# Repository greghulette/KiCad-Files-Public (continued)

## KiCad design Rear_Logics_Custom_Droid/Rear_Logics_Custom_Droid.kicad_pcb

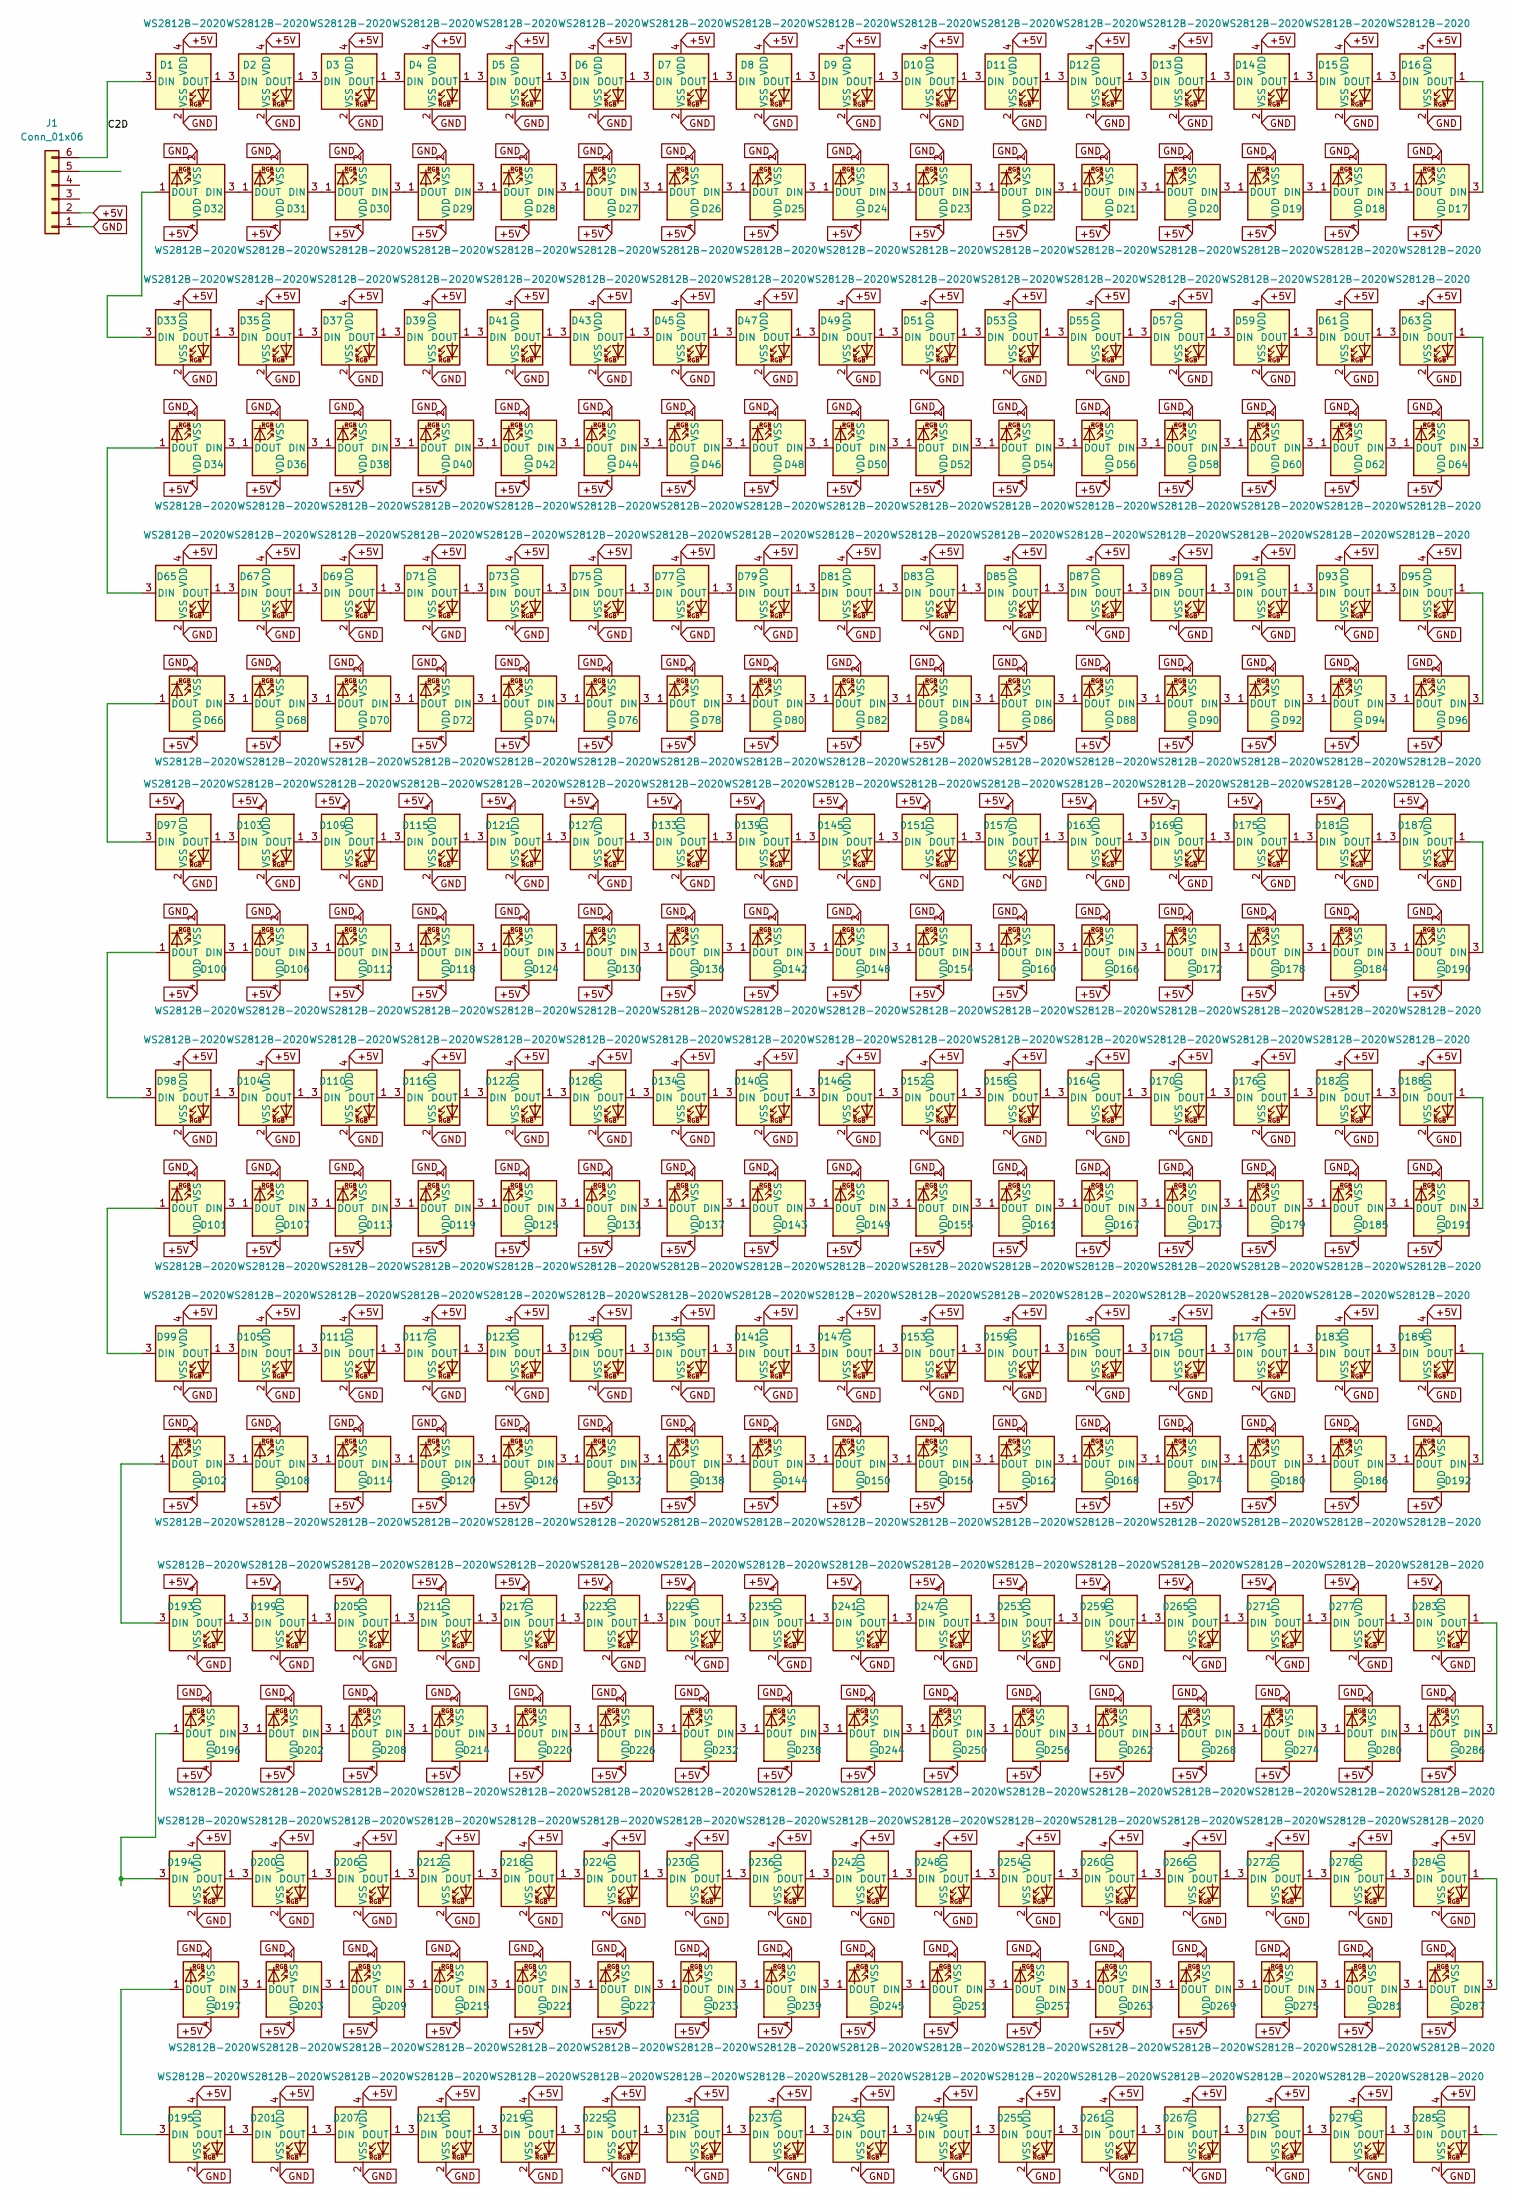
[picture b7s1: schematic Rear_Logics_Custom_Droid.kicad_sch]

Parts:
D1, D2, D3, D4, D5, D6, D7, D8, D9, D10, D11, D12, D13, D14, D15, D16, D17, D18, D19, D20, D21, D22, D23, D24, D25, D26, D27, D28, D29, D30, D31, D32, D33, D34, D35, D36, D37, D38, D39, D40, D41, D42, D43, D44, D45, D46, D47, D48, D49, D50, D51, D52, D53, D54, D55, D56, D57, D58, D59, D60, D61, D62, D63, D64, D65, D66, D67, D68, D69, D70, D71, D72, D73, D74, D75, D76, D77, D78, D79, D80, D81, D82, D83, D84, D85, D86, D87, D88, D89, D90, D91, D92, D93, D94, D95, D96, D97, D98, D99, D100, D101, D102, D103, D104, D105, D106, D107, D108, D109, D110, D111, D112, D113, D114, D115, D116, D117, D118, D119, D120, D121, D122, D123, D124, D125, D126, D127, D128, D129, D130, D131, D132, D133, D134, D135, D136, D137, D138, D139, D140, D141, D142, D143, D144, D145, D146, D147, D148, D149, D150, D151, D152, D153, D154, D155, D156, D157, D158, D159, D160, D161, D162, D163, D164, D165, D166, D167, D168, D169, D170, D171, D172, D173, D174, D175, D176, D177, D178, D179, D180, D181, D182, D183, D184, D185, D186, D187, D188, D189, D190, D191, D192, D193, D194, D195, D196, D197, D199, D200, D201, D202, D203, D205, D206, D207, D208, D209, D211, D212, D213, D214, D215, D217, D218, D219, D220, D221, D223, D224, D225, D226, D227, D229, D230, D231, D232, D233, D235, D236, D237, D238, D239, D241, D242, D243, D244, D245, D247, D248, D249, D250, D251, D253, D254, D255, D256, D257, D259, D260, D261, D262, D263, D265, D266, D267, D268, D269, D271, D272, D273, D274, D275, D277, D278, D279, D280, D281, D283, D284, D285, D286, D287: WS2812B-2020; LED_WS2812B-2020_PLCC4_2.0x2.0mm
J1: Conn_01x06; PinHeader_1x06_P2.54mm_Vertical

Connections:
+5V: D1.4 (VDD), D2.4 (VDD), D3.4 (VDD), D4.4 (VDD), D5.4 (VDD), D6.4 (VDD), D7.4 (VDD), D8.4 (VDD), D9.4 (VDD), D10.4 (VDD), D11.4 (VDD), D12.4 (VDD), D13.4 (VDD), D14.4 (VDD), D15.4 (VDD), D16.4 (VDD), D17.4 (VDD), D18.4 (VDD), D19.4 (VDD), D20.4 (VDD), D21.4 (VDD), D22.4 (VDD), D23.4 (VDD), D24.4 (VDD), D25.4 (VDD), D26.4 (VDD), D27.4 (VDD), D28.4 (VDD), D29.4 (VDD), D30.4 (VDD), D31.4 (VDD), D32.4 (VDD), D33.4 (VDD), D34.4 (VDD), D35.4 (VDD), D36.4 (VDD), D37.4 (VDD), D38.4 (VDD), D39.4 (VDD), D40.4 (VDD), D41.4 (VDD), D42.4 (VDD), D43.4 (VDD), D44.4 (VDD), D45.4 (VDD), D46.4 (VDD), D47.4 (VDD), D48.4 (VDD), D49.4 (VDD), D50.4 (VDD), D51.4 (VDD), D52.4 (VDD), D53.4 (VDD), D54.4 (VDD), D55.4 (VDD), D56.4 (VDD), D57.4 (VDD), D58.4 (VDD), D59.4 (VDD), D60.4 (VDD), D61.4 (VDD), D62.4 (VDD), D63.4 (VDD), D64.4 (VDD), D65.4 (VDD), D66.4 (VDD), D67.4 (VDD), D68.4 (VDD), D69.4 (VDD), D70.4 (VDD), D71.4 (VDD), D72.4 (VDD), D73.4 (VDD), D74.4 (VDD), D75.4 (VDD), D76.4 (VDD), D77.4 (VDD), D78.4 (VDD), D79.4 (VDD), D80.4 (VDD), D81.4 (VDD), D82.4 (VDD), D83.4 (VDD), D84.4 (VDD), D85.4 (VDD), D86.4 (VDD), D87.4 (VDD), D88.4 (VDD), D89.4 (VDD), D90.4 (VDD), D91.4 (VDD), D92.4 (VDD), D93.4 (VDD), D94.4 (VDD), D95.4 (VDD), D96.4 (VDD), D97.4 (VDD), D98.4 (VDD), D99.4 (VDD), D100.4 (VDD), D101.4 (VDD), D102.4 (VDD), D103.4 (VDD), D104.4 (VDD), D105.4 (VDD), D106.4 (VDD), D107.4 (VDD), D108.4 (VDD), D109.4 (VDD), D110.4 (VDD), D111.4 (VDD), D112.4 (VDD), D113.4 (VDD), D114.4 (VDD), D115.4 (VDD), D116.4 (VDD), D117.4 (VDD), D118.4 (VDD), D119.4 (VDD), D120.4 (VDD), D121.4 (VDD), D122.4 (VDD), D123.4 (VDD), D124.4 (VDD), D125.4 (VDD), D126.4 (VDD), D127.4 (VDD), D128.4 (VDD), D129.4 (VDD), D130.4 (VDD), D131.4 (VDD), D132.4 (VDD), D133.4 (VDD), D134.4 (VDD), D135.4 (VDD), D136.4 (VDD), D137.4 (VDD), D138.4 (VDD), D139.4 (VDD), D140.4 (VDD), D141.4 (VDD), D142.4 (VDD), D143.4 (VDD), D144.4 (VDD), D145.4 (VDD), D146.4 (VDD), D147.4 (VDD), D148.4 (VDD), D149.4 (VDD), D150.4 (VDD), D151.4 (VDD), D152.4 (VDD), D153.4 (VDD), D154.4 (VDD), D155.4 (VDD), D156.4 (VDD), D157.4 (VDD), D158.4 (VDD), D159.4 (VDD), D160.4 (VDD), D161.4 (VDD), D162.4 (VDD), D163.4 (VDD), D164.4 (VDD), D165.4 (VDD), D166.4 (VDD), D167.4 (VDD), D168.4 (VDD), D169.4 (VDD), D170.4 (VDD), D171.4 (VDD), D172.4 (VDD), D173.4 (VDD), D174.4 (VDD), D175.4 (VDD), D176.4 (VDD), D177.4 (VDD), D178.4 (VDD), D179.4 (VDD), D180.4 (VDD), D181.4 (VDD), D182.4 (VDD), D183.4 (VDD), D184.4 (VDD), D185.4 (VDD), D186.4 (VDD), D187.4 (VDD), D188.4 (VDD), D189.4 (VDD), D190.4 (VDD), D191.4 (VDD), D192.4 (VDD), D193.4 (VDD), D194.4 (VDD), D195.4 (VDD), D196.4 (VDD), D197.4 (VDD), D199.4 (VDD), D200.4 (VDD), D201.4 (VDD), D202.4 (VDD), D203.4 (VDD), D205.4 (VDD), D206.4 (VDD), D207.4 (VDD), D208.4 (VDD), D209.4 (VDD), D211.4 (VDD), D212.4 (VDD), D213.4 (VDD), D214.4 (VDD), D215.4 (VDD), D217.4 (VDD), D218.4 (VDD), D219.4 (VDD), D220.4 (VDD), D221.4 (VDD), D223.4 (VDD), D224.4 (VDD), D225.4 (VDD), D226.4 (VDD), D227.4 (VDD), D229.4 (VDD), D230.4 (VDD), D231.4 (VDD), D232.4 (VDD), D233.4 (VDD), D235.4 (VDD), D236.4 (VDD), D237.4 (VDD), D238.4 (VDD), D239.4 (VDD), D241.4 (VDD), D242.4 (VDD), D243.4 (VDD), D244.4 (VDD), D245.4 (VDD), D247.4 (VDD), D248.4 (VDD), D249.4 (VDD), D250.4 (VDD), D251.4 (VDD), D253.4 (VDD), D254.4 (VDD), D255.4 (VDD), D256.4 (VDD), D257.4 (VDD), D259.4 (VDD), D260.4 (VDD), D261.4 (VDD), D262.4 (VDD), D263.4 (VDD), D265.4 (VDD), D266.4 (VDD), D267.4 (VDD), D268.4 (VDD), D269.4 (VDD), D271.4 (VDD), D272.4 (VDD), D273.4 (VDD), D274.4 (VDD), D275.4 (VDD), D277.4 (VDD), D278.4 (VDD), D279.4 (VDD), D280.4 (VDD), D281.4 (VDD), D283.4 (VDD), D284.4 (VDD), D285.4 (VDD), D286.4 (VDD), D287.4 (VDD), J1.2
/C2D: D1.3 (DIN), J1.6
GND: D1.2 (VSS), D2.2 (VSS), D3.2 (VSS), D4.2 (VSS), D5.2 (VSS), D6.2 (VSS), D7.2 (VSS), D8.2 (VSS), D9.2 (VSS), D10.2 (VSS), D11.2 (VSS), D12.2 (VSS), D13.2 (VSS), D14.2 (VSS), D15.2 (VSS), D16.2 (VSS), D17.2 (VSS), D18.2 (VSS), D19.2 (VSS), D20.2 (VSS), D21.2 (VSS), D22.2 (VSS), D23.2 (VSS), D24.2 (VSS), D25.2 (VSS), D26.2 (VSS), D27.2 (VSS), D28.2 (VSS), D29.2 (VSS), D30.2 (VSS), D31.2 (VSS), D32.2 (VSS), D33.2 (VSS), D34.2 (VSS), D35.2 (VSS), D36.2 (VSS), D37.2 (VSS), D38.2 (VSS), D39.2 (VSS), D40.2 (VSS), D41.2 (VSS), D42.2 (VSS), D43.2 (VSS), D44.2 (VSS), D45.2 (VSS), D46.2 (VSS), D47.2 (VSS), D48.2 (VSS), D49.2 (VSS), D50.2 (VSS), D51.2 (VSS), D52.2 (VSS), D53.2 (VSS), D54.2 (VSS), D55.2 (VSS), D56.2 (VSS), D57.2 (VSS), D58.2 (VSS), D59.2 (VSS), D60.2 (VSS), D61.2 (VSS), D62.2 (VSS), D63.2 (VSS), D64.2 (VSS), D65.2 (VSS), D66.2 (VSS), D67.2 (VSS), D68.2 (VSS), D69.2 (VSS), D70.2 (VSS), D71.2 (VSS), D72.2 (VSS), D73.2 (VSS), D74.2 (VSS), D75.2 (VSS), D76.2 (VSS), D77.2 (VSS), D78.2 (VSS), D79.2 (VSS), D80.2 (VSS), D81.2 (VSS), D82.2 (VSS), D83.2 (VSS), D84.2 (VSS), D85.2 (VSS), D86.2 (VSS), D87.2 (VSS), D88.2 (VSS), D89.2 (VSS), D90.2 (VSS), D91.2 (VSS), D92.2 (VSS), D93.2 (VSS), D94.2 (VSS), D95.2 (VSS), D96.2 (VSS), D97.2 (VSS), D98.2 (VSS), D99.2 (VSS), D100.2 (VSS), D101.2 (VSS), D102.2 (VSS), D103.2 (VSS), D104.2 (VSS), D105.2 (VSS), D106.2 (VSS), D107.2 (VSS), D108.2 (VSS), D109.2 (VSS), D110.2 (VSS), D111.2 (VSS), D112.2 (VSS), D113.2 (VSS), D114.2 (VSS), D115.2 (VSS), D116.2 (VSS), D117.2 (VSS), D118.2 (VSS), D119.2 (VSS), D120.2 (VSS), D121.2 (VSS), D122.2 (VSS), D123.2 (VSS), D124.2 (VSS), D125.2 (VSS), D126.2 (VSS), D127.2 (VSS), D128.2 (VSS), D129.2 (VSS), D130.2 (VSS), D131.2 (VSS), D132.2 (VSS), D133.2 (VSS), D134.2 (VSS), D135.2 (VSS), D136.2 (VSS), D137.2 (VSS), D138.2 (VSS), D139.2 (VSS), D140.2 (VSS), D141.2 (VSS), D142.2 (VSS), D143.2 (VSS), D144.2 (VSS), D145.2 (VSS), D146.2 (VSS), D147.2 (VSS), D148.2 (VSS), D149.2 (VSS), D150.2 (VSS), D151.2 (VSS), D152.2 (VSS), D153.2 (VSS), D154.2 (VSS), D155.2 (VSS), D156.2 (VSS), D157.2 (VSS), D158.2 (VSS), D159.2 (VSS), D160.2 (VSS), D161.2 (VSS), D162.2 (VSS), D163.2 (VSS), D164.2 (VSS), D165.2 (VSS), D166.2 (VSS), D167.2 (VSS), D168.2 (VSS), D169.2 (VSS), D170.2 (VSS), D171.2 (VSS), D172.2 (VSS), D173.2 (VSS), D174.2 (VSS), D175.2 (VSS), D176.2 (VSS), D177.2 (VSS), D178.2 (VSS), D179.2 (VSS), D180.2 (VSS), D181.2 (VSS), D182.2 (VSS), D183.2 (VSS), D184.2 (VSS), D185.2 (VSS), D186.2 (VSS), D187.2 (VSS), D188.2 (VSS), D189.2 (VSS), D190.2 (VSS), D191.2 (VSS), D192.2 (VSS), D193.2 (VSS), D194.2 (VSS), D195.2 (VSS), D196.2 (VSS), D197.2 (VSS), D199.2 (VSS), D200.2 (VSS), D201.2 (VSS), D202.2 (VSS), D203.2 (VSS), D205.2 (VSS), D206.2 (VSS), D207.2 (VSS), D208.2 (VSS), D209.2 (VSS), D211.2 (VSS), D212.2 (VSS), D213.2 (VSS), D214.2 (VSS), D215.2 (VSS), D217.2 (VSS), D218.2 (VSS), D219.2 (VSS), D220.2 (VSS), D221.2 (VSS), D223.2 (VSS), D224.2 (VSS), D225.2 (VSS), D226.2 (VSS), D227.2 (VSS), D229.2 (VSS), D230.2 (VSS), D231.2 (VSS), D232.2 (VSS), D233.2 (VSS), D235.2 (VSS), D236.2 (VSS), D237.2 (VSS), D238.2 (VSS), D239.2 (VSS), D241.2 (VSS), D242.2 (VSS), D243.2 (VSS), D244.2 (VSS), D245.2 (VSS), D247.2 (VSS), D248.2 (VSS), D249.2 (VSS), D250.2 (VSS), D251.2 (VSS), D253.2 (VSS), D254.2 (VSS), D255.2 (VSS), D256.2 (VSS), D257.2 (VSS), D259.2 (VSS), D260.2 (VSS), D261.2 (VSS), D262.2 (VSS), D263.2 (VSS), D265.2 (VSS), D266.2 (VSS), D267.2 (VSS), D268.2 (VSS), D269.2 (VSS), D271.2 (VSS), D272.2 (VSS), D273.2 (VSS), D274.2 (VSS), D275.2 (VSS), D277.2 (VSS), D278.2 (VSS), D279.2 (VSS), D280.2 (VSS), D281.2 (VSS), D283.2 (VSS), D284.2 (VSS), D285.2 (VSS), D286.2 (VSS), D287.2 (VSS), J1.1
unnamed: D1.1 (DOUT), D2.3 (DIN)
unnamed: D2.1 (DOUT), D3.3 (DIN)
unnamed: D3.1 (DOUT), D4.3 (DIN)
unnamed: D4.1 (DOUT), D5.3 (DIN)
unnamed: D5.1 (DOUT), D6.3 (DIN)
unnamed: D6.1 (DOUT), D7.3 (DIN)
unnamed: D7.1 (DOUT), D8.3 (DIN)
unnamed: D8.1 (DOUT), D9.3 (DIN)
unnamed: D9.1 (DOUT), D10.3 (DIN)
unnamed: D10.1 (DOUT), D11.3 (DIN)
unnamed: D11.1 (DOUT), D12.3 (DIN)
unnamed: D12.1 (DOUT), D13.3 (DIN)
unnamed: D13.1 (DOUT), D14.3 (DIN)
unnamed: D14.1 (DOUT), D15.3 (DIN)
unnamed: D15.1 (DOUT), D16.3 (DIN)
unnamed: D16.1 (DOUT), D17.3 (DIN)
unnamed: D17.1 (DOUT), D18.3 (DIN)
unnamed: D18.1 (DOUT), D19.3 (DIN)
unnamed: D19.1 (DOUT), D20.3 (DIN)
unnamed: D20.1 (DOUT), D21.3 (DIN)
unnamed: D21.1 (DOUT), D22.3 (DIN)
unnamed: D22.1 (DOUT), D23.3 (DIN)
unnamed: D23.1 (DOUT), D24.3 (DIN)
unnamed: D24.1 (DOUT), D25.3 (DIN)
unnamed: D25.1 (DOUT), D26.3 (DIN)
unnamed: D26.1 (DOUT), D27.3 (DIN)
unnamed: D27.1 (DOUT), D28.3 (DIN)
unnamed: D28.1 (DOUT), D29.3 (DIN)
unnamed: D29.1 (DOUT), D30.3 (DIN)
unnamed: D30.1 (DOUT), D31.3 (DIN)
unnamed: D31.1 (DOUT), D32.3 (DIN)
unnamed: D32.1 (DOUT), D33.3 (DIN)
unnamed: D33.1 (DOUT), D35.3 (DIN)
unnamed: D34.3 (DIN), D36.1 (DOUT)
unnamed: D34.1 (DOUT), D65.3 (DIN)
unnamed: D35.1 (DOUT), D37.3 (DIN)
unnamed: D36.3 (DIN), D38.1 (DOUT)
unnamed: D37.1 (DOUT), D39.3 (DIN)
unnamed: D38.3 (DIN), D40.1 (DOUT)
unnamed: D39.1 (DOUT), D41.3 (DIN)
unnamed: D40.3 (DIN), D42.1 (DOUT)
unnamed: D41.1 (DOUT), D43.3 (DIN)
unnamed: D42.3 (DIN), D44.1 (DOUT)
unnamed: D43.1 (DOUT), D45.3 (DIN)
unnamed: D44.3 (DIN), D46.1 (DOUT)
unnamed: D45.1 (DOUT), D47.3 (DIN)
unnamed: D46.3 (DIN), D48.1 (DOUT)
unnamed: D47.1 (DOUT), D49.3 (DIN)
unnamed: D48.3 (DIN), D50.1 (DOUT)
unnamed: D49.1 (DOUT), D51.3 (DIN)
unnamed: D50.3 (DIN), D52.1 (DOUT)
unnamed: D51.1 (DOUT), D53.3 (DIN)
unnamed: D52.3 (DIN), D54.1 (DOUT)
unnamed: D53.1 (DOUT), D55.3 (DIN)
unnamed: D54.3 (DIN), D56.1 (DOUT)
unnamed: D55.1 (DOUT), D57.3 (DIN)
unnamed: D56.3 (DIN), D58.1 (DOUT)
unnamed: D57.1 (DOUT), D59.3 (DIN)
unnamed: D58.3 (DIN), D60.1 (DOUT)
unnamed: D59.1 (DOUT), D61.3 (DIN)
unnamed: D60.3 (DIN), D62.1 (DOUT)
unnamed: D61.1 (DOUT), D63.3 (DIN)
unnamed: D62.3 (DIN), D64.1 (DOUT)
unnamed: D63.1 (DOUT), D64.3 (DIN)
unnamed: D65.1 (DOUT), D67.3 (DIN)
unnamed: D66.3 (DIN), D68.1 (DOUT)
unnamed: D66.1 (DOUT), D97.3 (DIN)
unnamed: D67.1 (DOUT), D69.3 (DIN)
unnamed: D68.3 (DIN), D70.1 (DOUT)
unnamed: D69.1 (DOUT), D71.3 (DIN)
unnamed: D70.3 (DIN), D72.1 (DOUT)
unnamed: D71.1 (DOUT), D73.3 (DIN)
unnamed: D72.3 (DIN), D74.1 (DOUT)
unnamed: D73.1 (DOUT), D75.3 (DIN)
unnamed: D74.3 (DIN), D76.1 (DOUT)
unnamed: D75.1 (DOUT), D77.3 (DIN)
unnamed: D76.3 (DIN), D78.1 (DOUT)
unnamed: D77.1 (DOUT), D79.3 (DIN)
unnamed: D78.3 (DIN), D80.1 (DOUT)
unnamed: D79.1 (DOUT), D81.3 (DIN)
unnamed: D80.3 (DIN), D82.1 (DOUT)
unnamed: D81.1 (DOUT), D83.3 (DIN)
unnamed: D82.3 (DIN), D84.1 (DOUT)
unnamed: D83.1 (DOUT), D85.3 (DIN)
unnamed: D84.3 (DIN), D86.1 (DOUT)
unnamed: D85.1 (DOUT), D87.3 (DIN)
unnamed: D86.3 (DIN), D88.1 (DOUT)
unnamed: D87.1 (DOUT), D89.3 (DIN)
unnamed: D88.3 (DIN), D90.1 (DOUT)
unnamed: D89.1 (DOUT), D91.3 (DIN)
unnamed: D90.3 (DIN), D92.1 (DOUT)
unnamed: D91.1 (DOUT), D93.3 (DIN)
unnamed: D92.3 (DIN), D94.1 (DOUT)
unnamed: D93.1 (DOUT), D95.3 (DIN)
unnamed: D94.3 (DIN), D96.1 (DOUT)
unnamed: D95.1 (DOUT), D96.3 (DIN)
unnamed: D100.3 (DIN), D106.1 (DOUT)
unnamed: D98.3 (DIN), D100.1 (DOUT)
unnamed: D101.3 (DIN), D107.1 (DOUT)
unnamed: D99.3 (DIN), D101.1 (DOUT)
unnamed: D102.3 (DIN), D108.1 (DOUT)
unnamed: D102.1 (DOUT), D193.3 (DIN)
unnamed: D97.1 (DOUT), D103.3 (DIN)
unnamed: D103.1 (DOUT), D109.3 (DIN)
unnamed: D98.1 (DOUT), D104.3 (DIN)
unnamed: D104.1 (DOUT), D110.3 (DIN)
unnamed: D99.1 (DOUT), D105.3 (DIN)
unnamed: D105.1 (DOUT), D111.3 (DIN)
unnamed: D106.3 (DIN), D112.1 (DOUT)
unnamed: D107.3 (DIN), D113.1 (DOUT)
unnamed: D108.3 (DIN), D114.1 (DOUT)
unnamed: D109.1 (DOUT), D115.3 (DIN)
unnamed: D110.1 (DOUT), D116.3 (DIN)
unnamed: D111.1 (DOUT), D117.3 (DIN)
unnamed: D112.3 (DIN), D118.1 (DOUT)
unnamed: D113.3 (DIN), D119.1 (DOUT)
unnamed: D114.3 (DIN), D120.1 (DOUT)
unnamed: D115.1 (DOUT), D121.3 (DIN)
unnamed: D116.1 (DOUT), D122.3 (DIN)
unnamed: D117.1 (DOUT), D123.3 (DIN)
unnamed: D118.3 (DIN), D124.1 (DOUT)
unnamed: D119.3 (DIN), D125.1 (DOUT)
unnamed: D120.3 (DIN), D126.1 (DOUT)
unnamed: D121.1 (DOUT), D127.3 (DIN)
unnamed: D122.1 (DOUT), D128.3 (DIN)
unnamed: D123.1 (DOUT), D129.3 (DIN)
unnamed: D124.3 (DIN), D130.1 (DOUT)
unnamed: D125.3 (DIN), D131.1 (DOUT)
unnamed: D126.3 (DIN), D132.1 (DOUT)
unnamed: D127.1 (DOUT), D133.3 (DIN)
unnamed: D128.1 (DOUT), D134.3 (DIN)
unnamed: D129.1 (DOUT), D135.3 (DIN)
unnamed: D130.3 (DIN), D136.1 (DOUT)
unnamed: D131.3 (DIN), D137.1 (DOUT)
unnamed: D132.3 (DIN), D138.1 (DOUT)
unnamed: D133.1 (DOUT), D139.3 (DIN)
unnamed: D134.1 (DOUT), D140.3 (DIN)
unnamed: D135.1 (DOUT), D141.3 (DIN)
unnamed: D136.3 (DIN), D142.1 (DOUT)
unnamed: D137.3 (DIN), D143.1 (DOUT)
unnamed: D138.3 (DIN), D144.1 (DOUT)
unnamed: D139.1 (DOUT), D145.3 (DIN)
unnamed: D140.1 (DOUT), D146.3 (DIN)
unnamed: D141.1 (DOUT), D147.3 (DIN)
unnamed: D142.3 (DIN), D148.1 (DOUT)
unnamed: D143.3 (DIN), D149.1 (DOUT)
unnamed: D144.3 (DIN), D150.1 (DOUT)
unnamed: D145.1 (DOUT), D151.3 (DIN)
unnamed: D146.1 (DOUT), D152.3 (DIN)
unnamed: D147.1 (DOUT), D153.3 (DIN)
unnamed: D148.3 (DIN), D154.1 (DOUT)
unnamed: D149.3 (DIN), D155.1 (DOUT)
unnamed: D150.3 (DIN), D156.1 (DOUT)
unnamed: D151.1 (DOUT), D157.3 (DIN)
unnamed: D152.1 (DOUT), D158.3 (DIN)
unnamed: D153.1 (DOUT), D159.3 (DIN)
unnamed: D154.3 (DIN), D160.1 (DOUT)
unnamed: D155.3 (DIN), D161.1 (DOUT)
unnamed: D156.3 (DIN), D162.1 (DOUT)
unnamed: D157.1 (DOUT), D163.3 (DIN)
unnamed: D158.1 (DOUT), D164.3 (DIN)
unnamed: D159.1 (DOUT), D165.3 (DIN)
unnamed: D160.3 (DIN), D166.1 (DOUT)
unnamed: D161.3 (DIN), D167.1 (DOUT)
unnamed: D162.3 (DIN), D168.1 (DOUT)
unnamed: D163.1 (DOUT), D169.3 (DIN)
unnamed: D164.1 (DOUT), D170.3 (DIN)
unnamed: D165.1 (DOUT), D171.3 (DIN)
unnamed: D166.3 (DIN), D172.1 (DOUT)
unnamed: D167.3 (DIN), D173.1 (DOUT)
unnamed: D168.3 (DIN), D174.1 (DOUT)
unnamed: D169.1 (DOUT), D175.3 (DIN)
unnamed: D170.1 (DOUT), D176.3 (DIN)
unnamed: D171.1 (DOUT), D177.3 (DIN)
unnamed: D172.3 (DIN), D178.1 (DOUT)
unnamed: D173.3 (DIN), D179.1 (DOUT)
unnamed: D174.3 (DIN), D180.1 (DOUT)
unnamed: D175.1 (DOUT), D181.3 (DIN)
unnamed: D176.1 (DOUT), D182.3 (DIN)
unnamed: D177.1 (DOUT), D183.3 (DIN)
unnamed: D178.3 (DIN), D184.1 (DOUT)
unnamed: D179.3 (DIN), D185.1 (DOUT)
unnamed: D180.3 (DIN), D186.1 (DOUT)
unnamed: D181.1 (DOUT), D187.3 (DIN)
unnamed: D182.1 (DOUT), D188.3 (DIN)
unnamed: D183.1 (DOUT), D189.3 (DIN)
unnamed: D184.3 (DIN), D190.1 (DOUT)
unnamed: D185.3 (DIN), D191.1 (DOUT)
unnamed: D186.3 (DIN), D192.1 (DOUT)
unnamed: D187.1 (DOUT), D190.3 (DIN)
unnamed: D188.1 (DOUT), D191.3 (DIN)
unnamed: D189.1 (DOUT), D192.3 (DIN)
unnamed: D193.1 (DOUT), D199.3 (DIN)
unnamed: D194.3 (DIN), D196.1 (DOUT)
unnamed: D194.1 (DOUT), D200.3 (DIN)
unnamed: D195.3 (DIN), D197.1 (DOUT)
unnamed: D195.1 (DOUT), D201.3 (DIN)
unnamed: D196.3 (DIN), D202.1 (DOUT)
unnamed: D197.3 (DIN), D203.1 (DOUT)
unnamed: D199.1 (DOUT), D205.3 (DIN)
unnamed: D200.1 (DOUT), D206.3 (DIN)
unnamed: D201.1 (DOUT), D207.3 (DIN)
unnamed: D202.3 (DIN), D208.1 (DOUT)
unnamed: D203.3 (DIN), D209.1 (DOUT)
unnamed: D205.1 (DOUT), D211.3 (DIN)
unnamed: D206.1 (DOUT), D212.3 (DIN)
unnamed: D207.1 (DOUT), D213.3 (DIN)
unnamed: D208.3 (DIN), D214.1 (DOUT)
unnamed: D209.3 (DIN), D215.1 (DOUT)
unnamed: D211.1 (DOUT), D217.3 (DIN)
unnamed: D212.1 (DOUT), D218.3 (DIN)
unnamed: D213.1 (DOUT), D219.3 (DIN)
unnamed: D214.3 (DIN), D220.1 (DOUT)
unnamed: D215.3 (DIN), D221.1 (DOUT)
unnamed: D217.1 (DOUT), D223.3 (DIN)
unnamed: D218.1 (DOUT), D224.3 (DIN)
unnamed: D219.1 (DOUT), D225.3 (DIN)
unnamed: D220.3 (DIN), D226.1 (DOUT)
unnamed: D221.3 (DIN), D227.1 (DOUT)
unnamed: D223.1 (DOUT), D229.3 (DIN)
unnamed: D224.1 (DOUT), D230.3 (DIN)
unnamed: D225.1 (DOUT), D231.3 (DIN)
unnamed: D226.3 (DIN), D232.1 (DOUT)
unnamed: D227.3 (DIN), D233.1 (DOUT)
unnamed: D229.1 (DOUT), D235.3 (DIN)
unnamed: D230.1 (DOUT), D236.3 (DIN)
unnamed: D231.1 (DOUT), D237.3 (DIN)
unnamed: D232.3 (DIN), D238.1 (DOUT)
unnamed: D233.3 (DIN), D239.1 (DOUT)
unnamed: D235.1 (DOUT), D241.3 (DIN)
unnamed: D236.1 (DOUT), D242.3 (DIN)
unnamed: D237.1 (DOUT), D243.3 (DIN)
unnamed: D238.3 (DIN), D244.1 (DOUT)
unnamed: D239.3 (DIN), D245.1 (DOUT)
unnamed: D241.1 (DOUT), D247.3 (DIN)
unnamed: D242.1 (DOUT), D248.3 (DIN)
unnamed: D243.1 (DOUT), D249.3 (DIN)
unnamed: D244.3 (DIN), D250.1 (DOUT)
unnamed: D245.3 (DIN), D251.1 (DOUT)
unnamed: D247.1 (DOUT), D253.3 (DIN)
unnamed: D248.1 (DOUT), D254.3 (DIN)
unnamed: D249.1 (DOUT), D255.3 (DIN)
unnamed: D250.3 (DIN), D256.1 (DOUT)
unnamed: D251.3 (DIN), D257.1 (DOUT)
unnamed: D253.1 (DOUT), D259.3 (DIN)
unnamed: D254.1 (DOUT), D260.3 (DIN)
unnamed: D255.1 (DOUT), D261.3 (DIN)
unnamed: D256.3 (DIN), D262.1 (DOUT)
unnamed: D257.3 (DIN), D263.1 (DOUT)
unnamed: D259.1 (DOUT), D265.3 (DIN)
unnamed: D260.1 (DOUT), D266.3 (DIN)
unnamed: D261.1 (DOUT), D267.3 (DIN)
unnamed: D262.3 (DIN), D268.1 (DOUT)
unnamed: D263.3 (DIN), D269.1 (DOUT)
unnamed: D265.1 (DOUT), D271.3 (DIN)
unnamed: D266.1 (DOUT), D272.3 (DIN)
unnamed: D267.1 (DOUT), D273.3 (DIN)
unnamed: D268.3 (DIN), D274.1 (DOUT)
unnamed: D269.3 (DIN), D275.1 (DOUT)
unnamed: D271.1 (DOUT), D277.3 (DIN)
unnamed: D272.1 (DOUT), D278.3 (DIN)
unnamed: D273.1 (DOUT), D279.3 (DIN)
unnamed: D274.3 (DIN), D280.1 (DOUT)
unnamed: D275.3 (DIN), D281.1 (DOUT)
unnamed: D277.1 (DOUT), D283.3 (DIN)
unnamed: D278.1 (DOUT), D284.3 (DIN)
unnamed: D279.1 (DOUT), D285.3 (DIN)
unnamed: D280.3 (DIN), D286.1 (DOUT)
unnamed: D281.3 (DIN), D287.1 (DOUT)
unnamed: D283.1 (DOUT), D286.3 (DIN)
unnamed: D284.1 (DOUT), D287.3 (DIN)

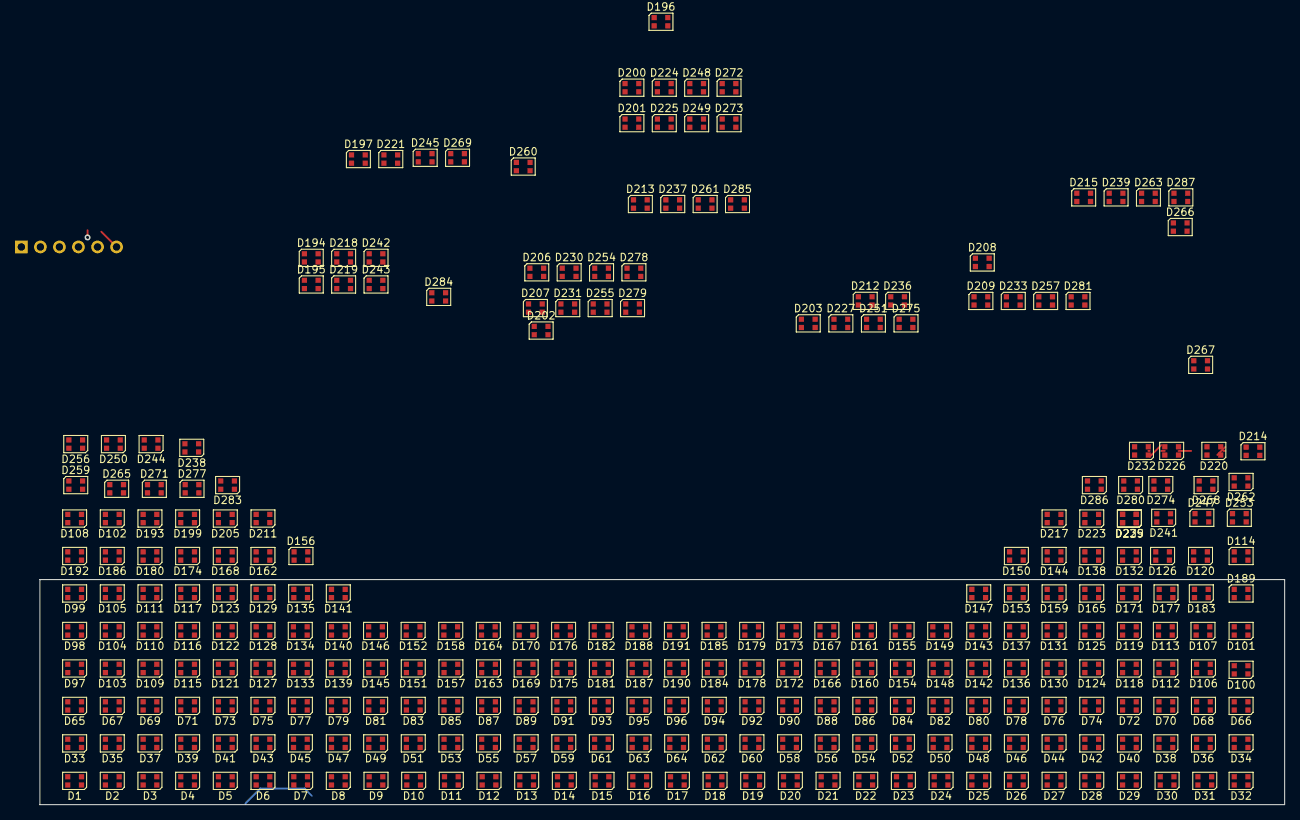
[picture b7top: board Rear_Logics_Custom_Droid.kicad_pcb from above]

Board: 2 copper layers, 166.1 x 30.0 mm, 273 parts (1 on the bottom side), 274 nets.

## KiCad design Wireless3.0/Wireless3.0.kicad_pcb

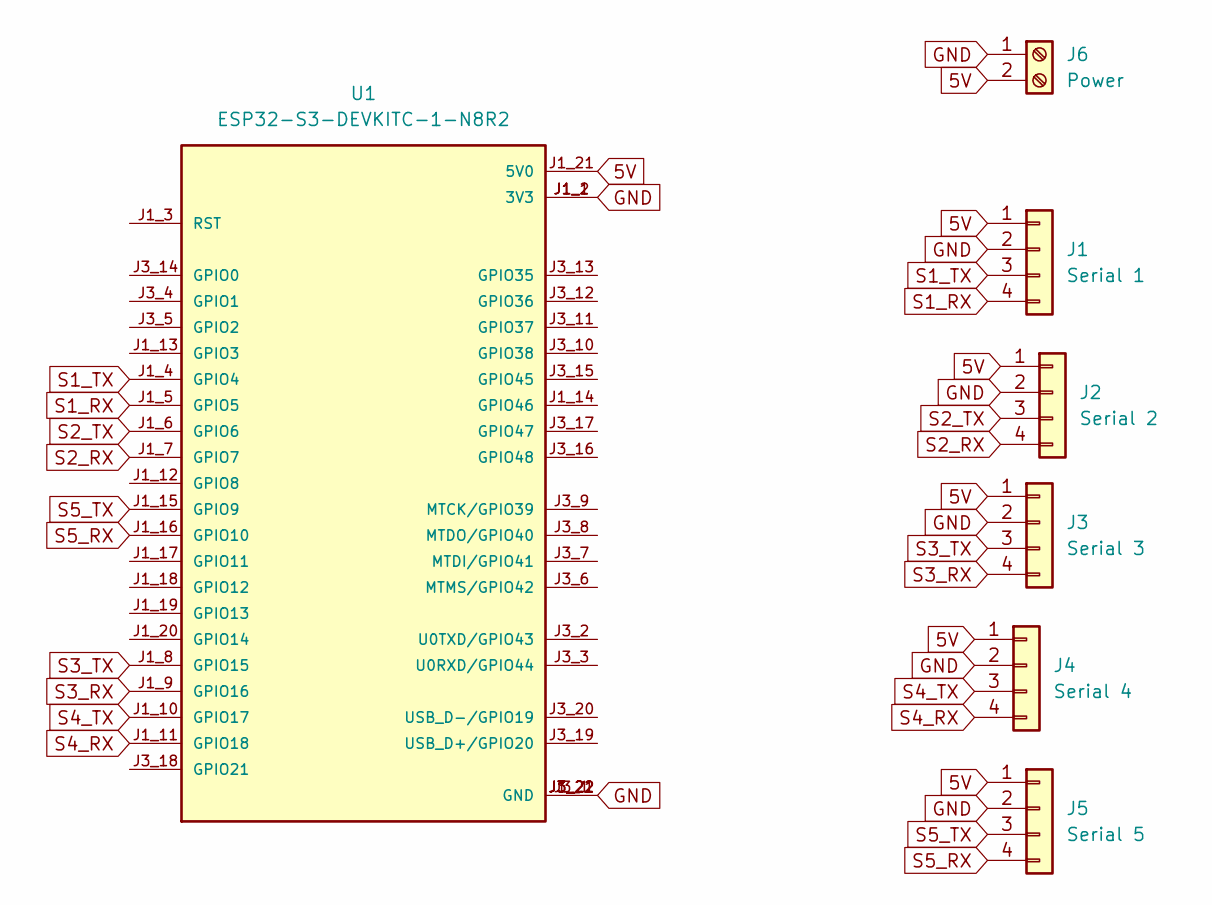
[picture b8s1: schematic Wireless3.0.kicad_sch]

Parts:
J1: Serial 1; PinHeader_1x04_P2.54mm_Vertical
J2: Serial 2; PinHeader_1x04_P2.54mm_Vertical
J3: Serial 3; PinHeader_1x04_P2.54mm_Vertical
J4: Serial 4; PinHeader_1x04_P2.54mm_Vertical
J5: Serial 5; PinHeader_1x04_P2.54mm_Vertical
J6: Power; TerminalBlock_Phoenix_MKDS-1,5-2-5.08_1x02_P5.08mm_Horizont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
U1: ESP32-S3-DEVKITC-1-N8R2; XCVR_ESP32-S3-DEVKITC-1-N8R2; PARTREV V1

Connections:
5V: J1.1, J2.1, J3.1, J4.1, J5.1, J6.2, U1.J1_21 (5V0)
GND: J1.2, J2.2, J3.2, J4.2, J5.2, J6.1, U1.J1_1 (3V3), U1.J1_2 (3V3), U1.J1_22 (GND), U1.J3_1 (GND), U1.J3_21 (GND), U1.J3_22 (GND)
S1_RX: J1.4, U1.J1_5 (GPIO5)
S1_TX: J1.3, U1.J1_4 (GPIO4)
S2_RX: J2.4, U1.J1_7 (GPIO7)
S2_TX: J2.3, U1.J1_6 (GPIO6)
S3_RX: J3.4, U1.J1_9 (GPIO16)
S3_TX: J3.3, U1.J1_8 (GPIO15)
S4_RX: J4.4, U1.J1_11 (GPIO18)
S4_TX: J4.3, U1.J1_10 (GPIO17)
S5_RX: J5.4, U1.J1_16 (GPIO10)
S5_TX: J5.3, U1.J1_15 (GPIO9)

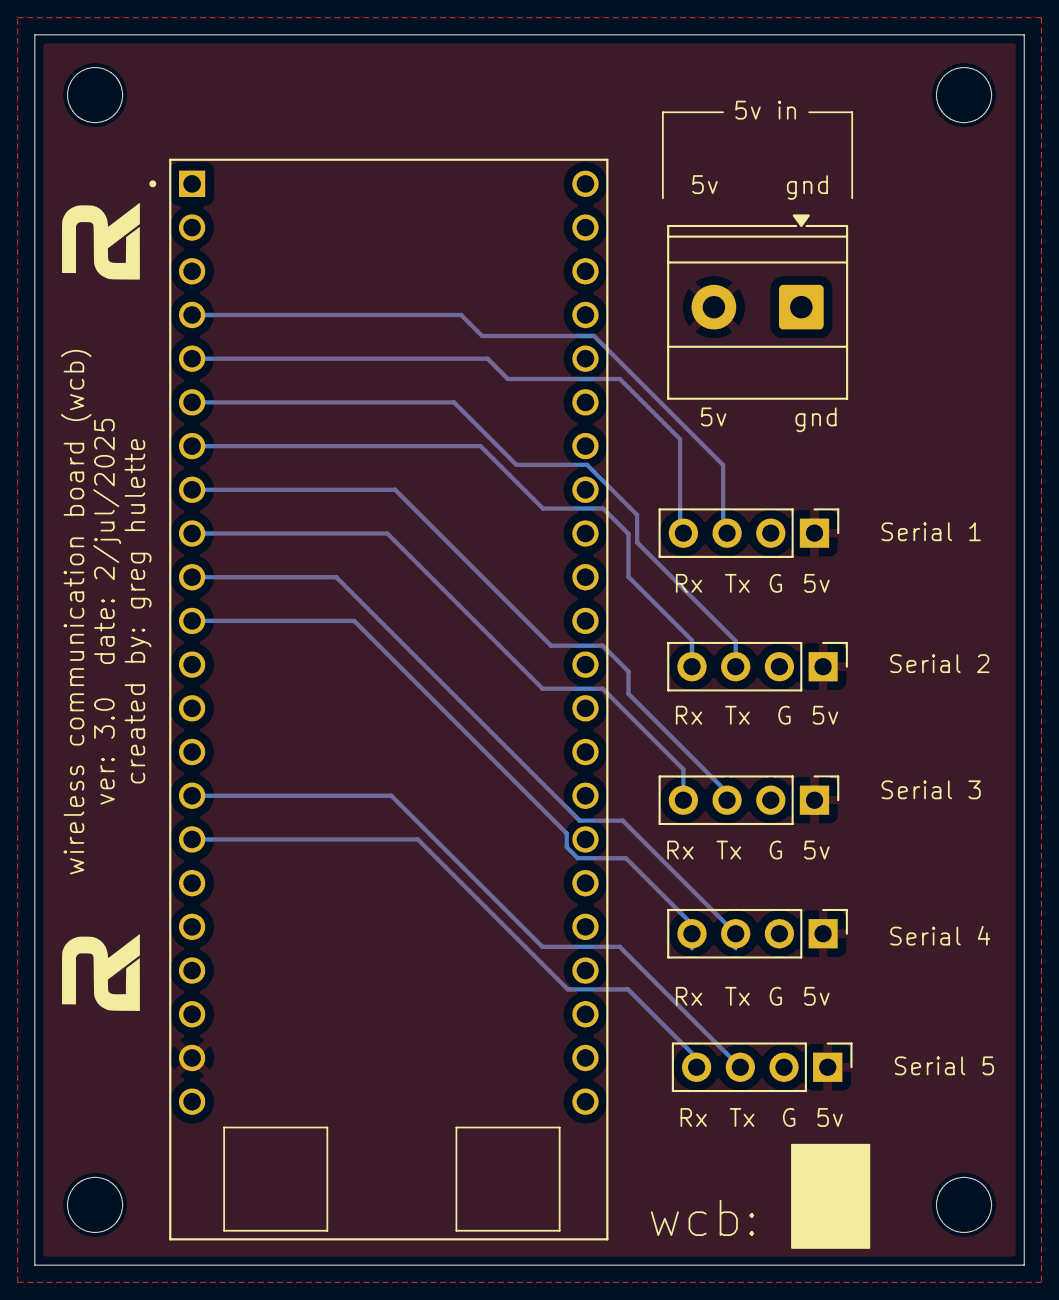
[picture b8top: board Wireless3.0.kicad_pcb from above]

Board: 2 copper layers, 57.5 x 71.5 mm, 7 parts (0 on the bottom side), 12 nets.

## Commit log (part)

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2022-08-31 Initial Push
2022-09-01 Added the Dome Controller
2022-09-01 Updated the body Controller to have SMA and u.fl interfaces for the 32U
2022-09-21 Updates to some files
2022-10-03 updates to the boards
2022-11-17 Added Uppity Spinner
2022-11-23 Working on new body control board
2022-12-02 Added a lot since last check in
2022-12-05 Added a 4th pin to the dome logics controller to support the curved LEDs, in case anyone wants to order them besides myself
2022-12-08 added LED PCBs
2022-12-08 Cleaning up the folder structure and removed old boards
2023-01-06 creating more boards
2023-01-18 Added custom libraries and updated the Kill Switch (Remote)
2023-01-19 updates to backups
2023-02-02 Working on boards
2023-04-06 A lot of updates. Too much to describe
2023-04-12 Working on new kill switch boards
2023-04-13 Updated the servo controller to adjust for the 4 pin molex header's alignment pin
2023-04-13 Updating the Kill Switch Droid side
2023-04-13 Updates to the kill switches
2023-04-14 changed folder name
2023-08-17 some minor updates
2023-08-29 didn't change too much
2023-09-06 notyhing new
2023-09-11 Working on Body Controller V1.2
2023-12-07 Lots of changes
2023-12-27 added some backups. not much changed.
2024-01-26 updated WCB
2024-02-24 Added backups.
    Not much changed. Just added backups.
2024-04-09 working on slip ring
2025-01-16 Updated C3P0 Controller
2025-07-03 added wcb3
2025-07-03 moved things around in the wcb3.0 folder
2025-07-03 no changes
2025-07-09 updated wcb 3.0 to 3.1
2025-10-03 added files.
2026-04-25 added components to hh
2026-05-29 sabe
2026-06-02 added stepstl
